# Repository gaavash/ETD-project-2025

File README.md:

# ETD-project-2025
final project of ETD H-bridge

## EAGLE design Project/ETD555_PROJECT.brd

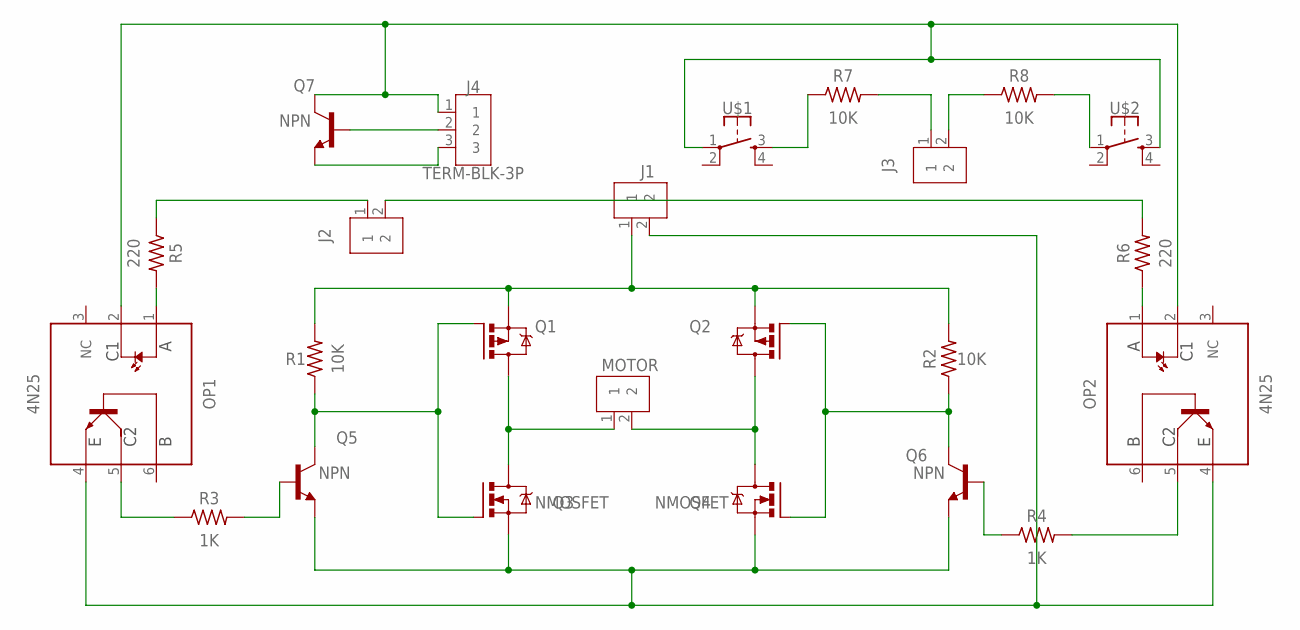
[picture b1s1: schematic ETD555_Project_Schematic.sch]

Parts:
J1, J2, J3: TERM-BLK-2P; TERMBLK_508-2N
J4: TERM-BLK-3P; TERMBLK_254-3N
MOTOR: TERM-BLK-2P; TERMBLK_508-2N
OP1, OP2: 4N25; DIP762W60P254L712H480Q6B
Q1, Q2: PMOSFET; TO220BV
Q3, Q4: NMOSFET; TO220BV
Q5, Q6, Q7: NPN; TO92
R1, R2, R7, R8: 10K; RESAD724W46L381D178B
R3, R4: 1K; RESAD724W46L381D178B
R5, R6: 220; RESAD724W46L381D178B
U$1, U$2: SWITCH_MOMENTARY; SWITCH-MOMENTARY-PTH-6.5MM

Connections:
unnamed: MOTOR.2, Q2.D, Q4.D
unnamed: MOTOR.1, Q1.D, Q3.D
unnamed: J1.1, Q1.S, Q2.S, R1.2, R2.2
unnamed: OP2.1 (A), R6.1
unnamed: Q1.G, Q3.G, Q5.3 (C), R1.1
unnamed: J1.2, OP1.4 (E), OP2.4 (E), Q3.S, Q4.S, Q5.1 (E), Q6.1 (E)
unnamed: Q6.2 (B), R4.1
unnamed: Q5.2 (B), R3.2
unnamed: Q2.G, Q4.G, Q6.3 (C), R2.1
unnamed: J2.1, R5.1
unnamed: OP1.5 (C2), R3.1
unnamed: OP1.1 (A), R5.2
unnamed: J2.2, R6.2
unnamed: J4.2, Q7.2 (B)
unnamed: J4.1, OP1.2 (C1), OP2.2 (C1), Q7.3 (C), U$1.1, U$2.3
unnamed: J4.3, Q7.1 (E)
unnamed: R7.1, U$1.3
unnamed: R8.2, U$2.1
unnamed: OP2.5 (C2), R4.2
unnamed: J3.1, R7.2
unnamed: J3.2, R8.1

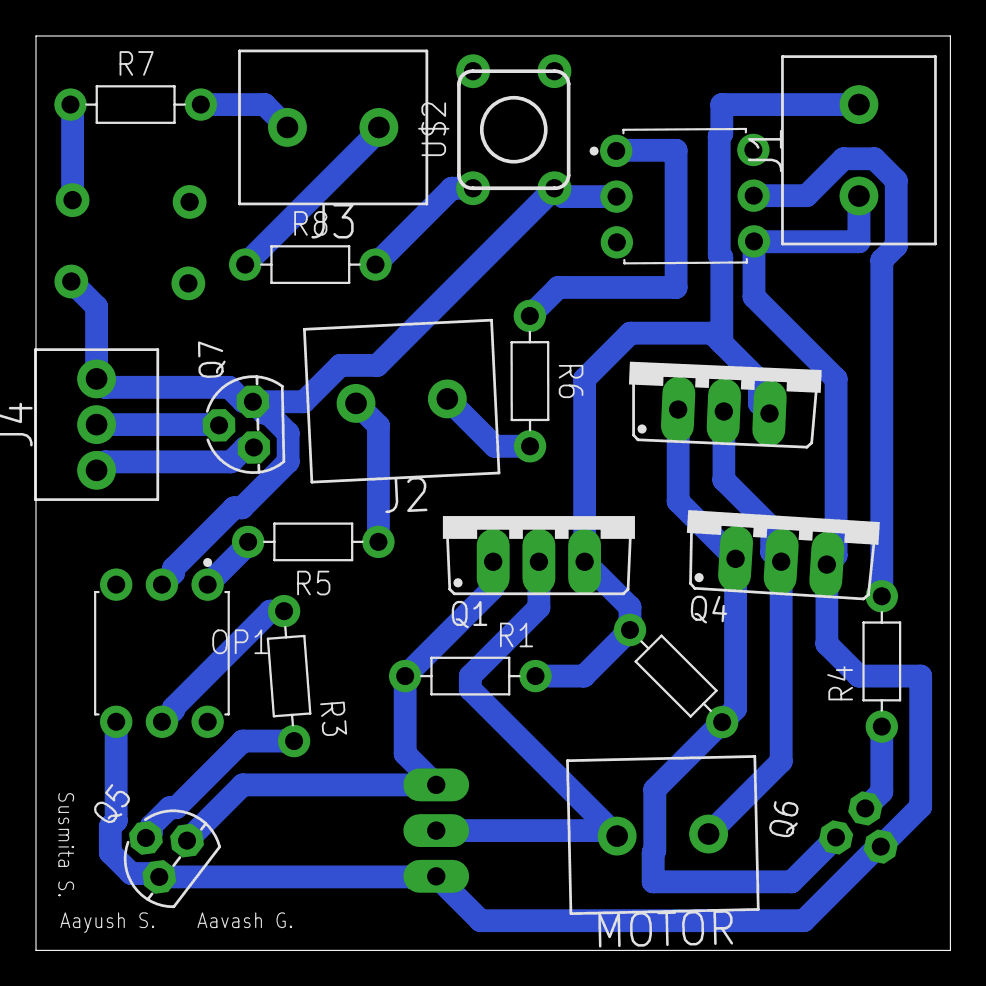
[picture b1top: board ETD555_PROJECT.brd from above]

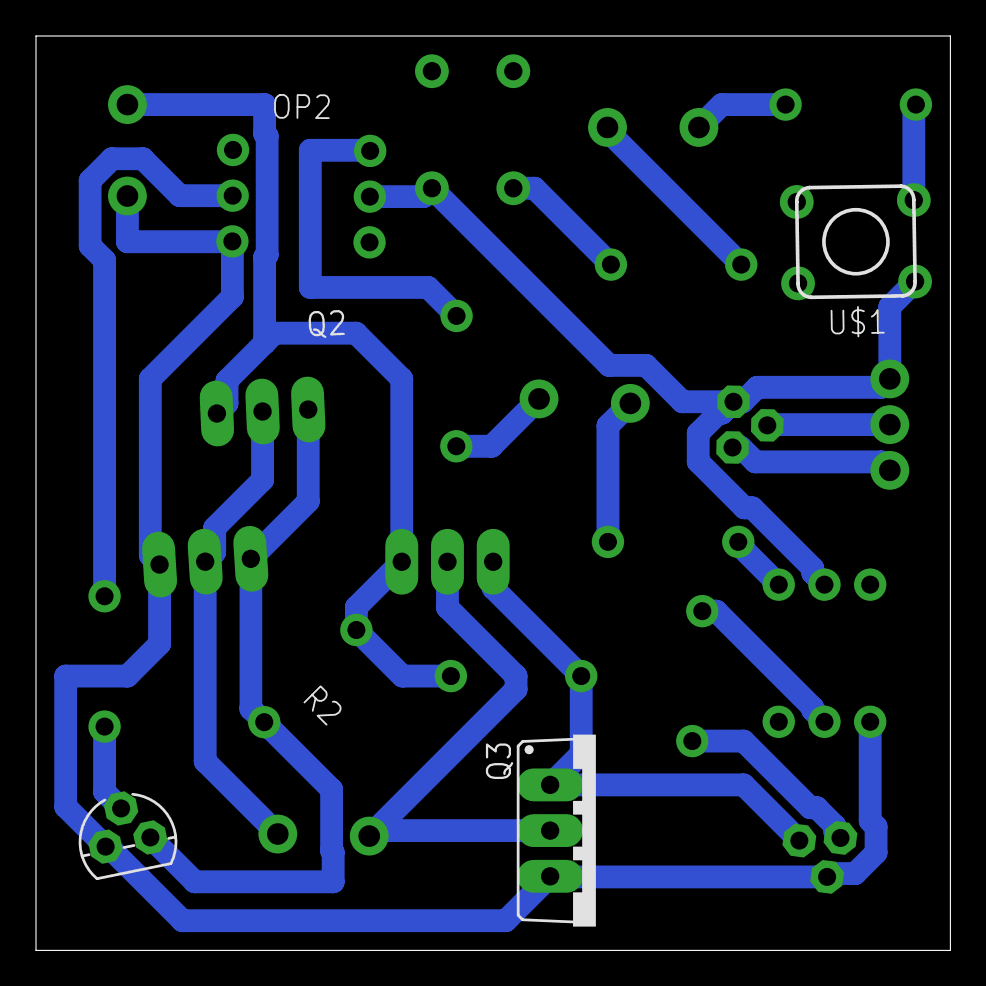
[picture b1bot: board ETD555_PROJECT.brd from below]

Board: 2 copper layers, 50.8 x 50.8 mm, 24 parts (3 on the bottom side), 21 nets.
